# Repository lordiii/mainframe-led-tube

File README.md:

# TODO: README

See also:
https://github.com/XenGi/teensy_library

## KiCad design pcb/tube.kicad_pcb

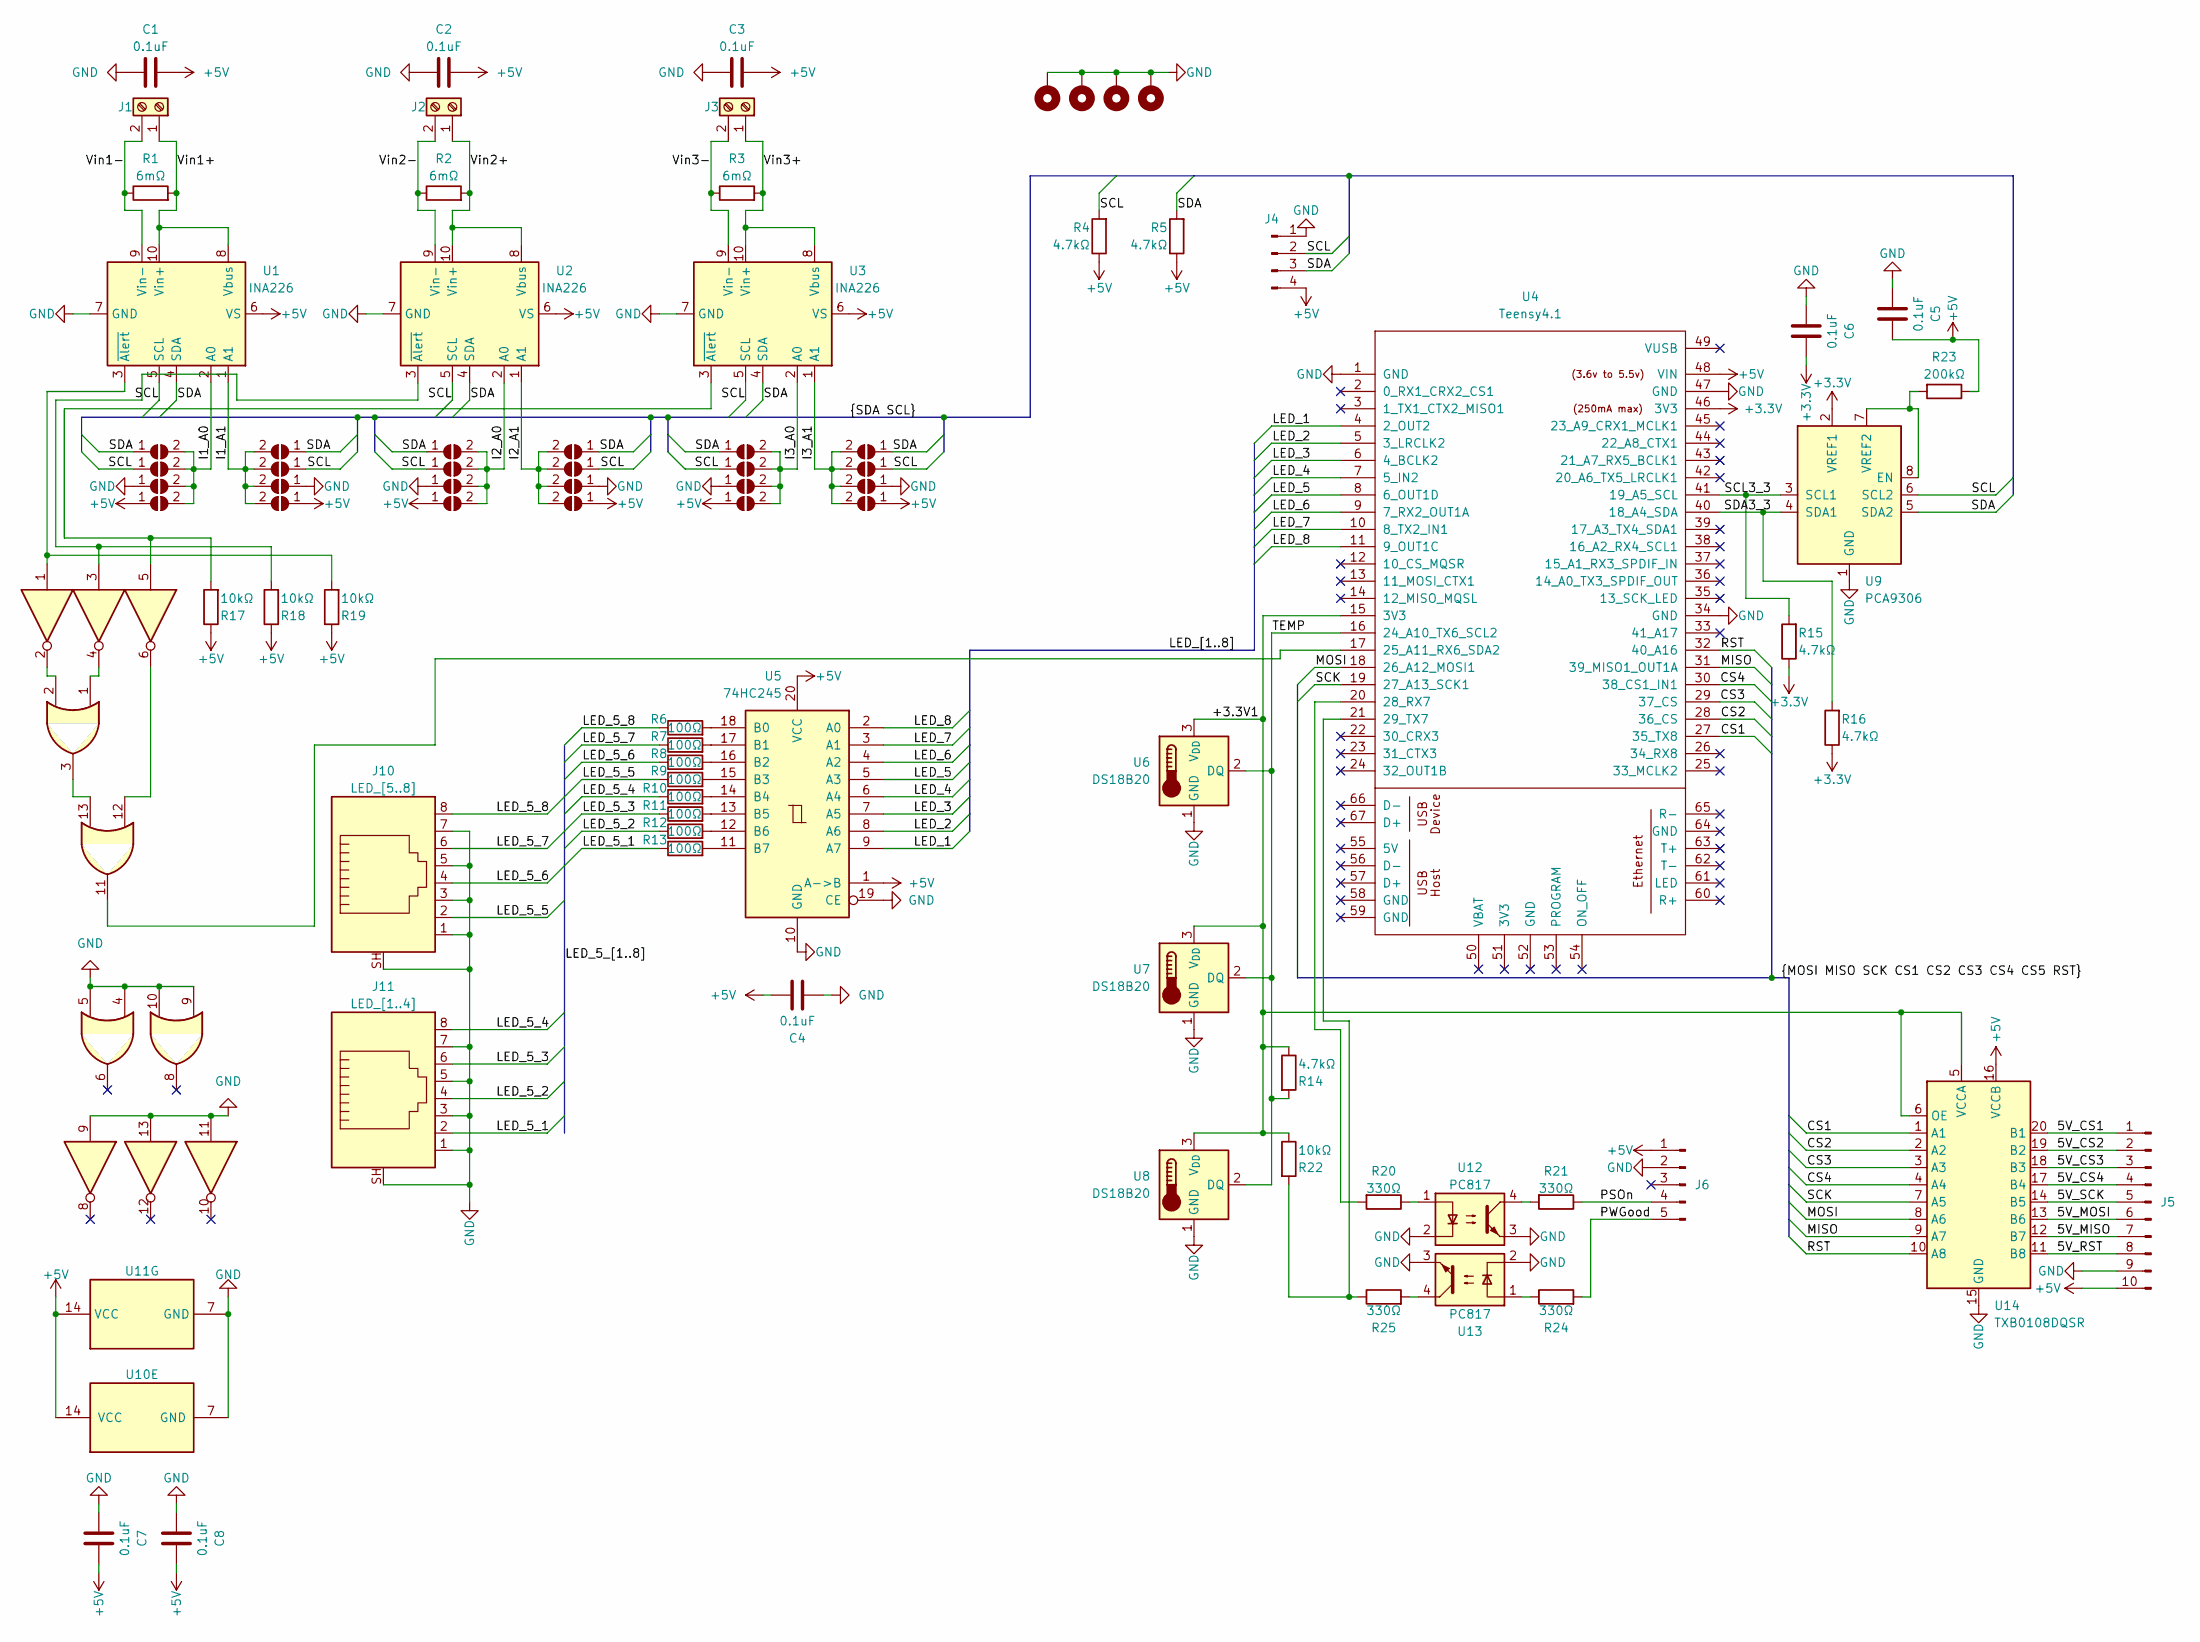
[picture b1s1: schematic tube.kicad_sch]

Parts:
C1, C2, C3, C4, C5, C6, C7, C8: 0.1uF; C_0805_2012Metric
H1, H2, H3, H4: MountingHole_Pad; MountingHole_2.2mm_M2_Pad
J1, J2, J3: Screw_Terminal_01x02; HB9500_1x02_P9.5mm_Screw_terminal
J4: Conn_01x04_Pin; PinHeader_1x04_P2.54mm_Vertical
J5: Conn_01x10_Pin; PinHeader_1x10_P2.54mm_Vertical
J6: Conn_01x05_Pin; 15EDG_Plug-in_Terminal_5x05_P2.54mm_Horizontal
J10: LED_[5..8]; RJ45_Ninigi_GE
J11: LED_[1..4]; RJ45_Ninigi_GE
JP1, JP2, JP3, JP4, JP5, JP6, JP7, JP8, JP9, JP10, JP11, JP12, JP13, JP14, JP15, JP16, JP17, JP18, JP19, JP20, JP21, JP22, JP23, JP24: SolderJumper_2_Open; SolderJumper-2_P1.3mm_Open_TrianglePad1.0x1.5mm
R1, R2, R3: 6mΩ; R_2512_6332Metric
R4, R5, R14, R15, R16: 4.7kΩ; R_0805_2012Metric
R6, R7, R8, R9, R10, R11, R12, R13: 100Ω; R_0805_2012Metric
R17, R18, R19, R22: 10kΩ; R_0805_2012Metric
R20, R21, R24, R25: 330Ω; R_0805_2012Metric
R23: 200kΩ; R_0805_2012Metric
U1, U2, U3: INA226; VSSOP-10_3x3mm_P0.5mm
U4: Teensy4.1; DIP-48_W15.24mm
U5: 74HC245; SSOP-20_4.4x6.5mm_P0.65mm
U6, U7, U8: DS18B20; PinHeader_1x03_P2.54mm_Vertical
U9: PCA9306; VSSOP-8_2.3x2mm_P0.5mm
U10: 74LS32; SO-14_3.9x8.65mm_P1.27mm
U11: 74AHC04; SO-14_3.9x8.65mm_P1.27mm
U12, U13: PC817; DIP-4_W7.62mm
U14: TXB0108DQSR; HTSSOP-20-1EP_4.4x6.5mm_P0.65mm_EP2.74x3.86mm

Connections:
+3.3V: C6.2, R15.1, R16.1, U4.46 (3V3), U9.2 (VREF1)
+5V: C1.2, C2.2, C3.2, C4.2, C5.2, C7.2, C8.2, J4.4, J5.10, J6.1, JP4.1 (A), JP8.1 (A), JP15.1 (A), JP16.1 (A), JP23.1 (A), JP24.1 (A), R4.1, R5.1, R17.1, R18.1, R19.1, R23.1, U1.6 (VS), U2.6 (VS), U3.6 (VS), U4.48 (VIN), U5.1 (A->B), U5.20 (VCC), U10.14 (VCC), U11.14 (VCC), U14.16 (VCCB)
/5V_CS1: J5.1, U14.20 (B1)
/5V_CS2: J5.2, U14.19 (B2)
/5V_CS3: J5.3, U14.18 (B3)
/5V_CS4: J5.4, U14.17 (B4)
/5V_MISO: J5.7, U14.12 (B7)
/5V_MOSI: J5.6, U14.13 (B6)
/5V_RST: J5.8, U14.11 (B8)
/5V_SCK: J5.5, U14.14 (B5)
/+3.3V1: R14.1, R22.1, U4.15 (3V3), U6.3 (V_{DD}), U7.3 (V_{DD}), U8.3 (V_{DD}), U14.5 (VCCA), U14.6 (OE)
/CS1: U4.27 (35_TX8), U14.1 (A1)
/CS2: U4.28 (36_CS), U14.2 (A2)
/CS3: U4.29 (37_CS), U14.3 (A3)
/CS4: U4.30 (38_CS1_IN1), U14.4 (A4)
/I1_A0: JP1.2 (B), JP2.2 (B), JP3.2 (B), JP4.2 (B), U1.2 (A0)
/I1_A1: JP5.2 (B), JP6.2 (B), JP7.2 (B), JP8.2 (B), U1.1 (A1)
/I2_A0: JP9.2 (B), JP11.2 (B), JP13.2 (B), JP15.2 (B), U2.2 (A0)
/I2_A1: JP10.2 (B), JP12.2 (B), JP14.2 (B), JP16.2 (B), U2.1 (A1)
/I3_A0: JP17.2 (B), JP19.2 (B), JP21.2 (B), JP23.2 (B), U3.2 (A0)
/I3_A1: JP18.2 (B), JP20.2 (B), JP22.2 (B), JP24.2 (B), U3.1 (A1)
/LED_1: U4.4 (2_OUT2), U5.9 (A7)
/LED_2: U4.5 (3_LRCLK2), U5.8 (A6)
/LED_3: U4.6 (4_BCLK2), U5.7 (A5)
/LED_4: U4.7 (5_IN2), U5.6 (A4)
/LED_5: U4.8 (6_OUT1D), U5.5 (A3)
/LED_5_1: J11.2, R13.1
/LED_5_2: J11.4, R12.1
/LED_5_3: J11.6, R11.1
/LED_5_4: J11.8, R10.1
/LED_5_5: J10.2, R9.1
/LED_5_6: J10.4, R8.1
/LED_5_7: J10.6, R7.1
/LED_5_8: J10.8, R6.1
/LED_6: U4.9 (7_RX2_OUT1A), U5.4 (A2)
/LED_7: U4.10 (8_TX2_IN1), U5.3 (A1)
/LED_8: U4.11 (9_OUT1C), U5.2 (A0)
/MISO: U4.31 (39_MISO1_OUT1A), U14.9 (A7)
/MOSI: U4.18 (26_A12_MOSI1), U14.8 (A6)
/PSOn: J6.4, R21.1
/PWGood: J6.5, R24.2
/RST: U4.32 (40_A16), U14.10 (A8)
/SCK: U4.19 (27_A13_SCK1), U14.7 (A5)
/SCL: J4.2, JP2.1 (A), JP6.1 (A), JP11.1 (A), JP12.1 (A), JP19.1 (A), JP20.1 (A), R4.2, U1.5 (SCL), U2.5 (SCL), U3.5 (SCL), U9.6 (SCL2)
/SCL3_3: R15.2, U4.41 (19_A5_SCL), U9.3 (SCL1)
/SDA: J4.3, JP1.1 (A), JP5.1 (A), JP9.1 (A), JP10.1 (A), JP17.1 (A), JP18.1 (A), R5.2, U1.4 (SDA), U2.4 (SDA), U3.4 (SDA), U9.5 (SDA2)
/SDA3_3: R16.2, U4.40 (18_A4_SDA), U9.4 (SDA1)
/TEMP: R14.2, U4.16 (24_A10_TX6_SCL2), U6.2 (DQ), U7.2 (DQ), U8.2 (DQ)
/Vin1+: J1.1, R1.2, U1.8 (Vbus), U1.10 (Vin+)
/Vin1-: J1.2, R1.1, U1.9 (Vin-)
/Vin2+: J2.1, R2.2, U2.8 (Vbus), U2.10 (Vin+)
/Vin2-: J2.2, R2.1, U2.9 (Vin-)
/Vin3+: J3.1, R3.2, U3.8 (Vbus), U3.10 (Vin+)
/Vin3-: J3.2, R3.1, U3.9 (Vin-)
GND: C1.1, C2.1, C3.1, C4.1, C5.1, C6.1, C7.1, C8.1, H1.1, H2.1, H3.1, H4.1, J4.1, J5.9, J6.2, J10.1, J10.3, J10.5, J10.7, J10.SH, J11.1, J11.3, J11.5, J11.7, J11.SH, JP3.1 (A), JP7.1 (A), JP13.1 (A), JP14.1 (A), JP21.1 (A), JP22.1 (A), U1.7 (GND), U2.7 (GND), U3.7 (GND), U4.1 (GND), U4.34 (GND), U4.47 (GND), U5.10 (GND), U5.19 (CE), U6.1 (GND), U7.1 (GND), U8.1 (GND), U9.1 (GND), U10.4, U10.5, U10.7 (GND), U10.9, U10.10, U11.7 (GND), U11.9, U11.11, U11.13, U12.2, U12.3, U13.2, U13.3, U14.15 (GND)
unnamed: R20.1, U12.1
unnamed: R21.2, U12.4
unnamed: R24.1, U13.1
unnamed: R25.2, U13.4
unnamed: R19.2, U1.3 (~Alert), U11.1
unnamed: R18.2, U2.3 (~Alert), U11.3
unnamed: R17.2, U3.3 (~Alert), U11.5
unnamed: U4.17 (25_A11_RX6_SDA2), U10.11
unnamed: R20.2, U4.20 (28_RX7)
unnamed: R22.2, R25.1, U4.21 (29_TX7)
unnamed: R6.2, U5.18 (B0)
unnamed: R7.2, U5.17 (B1)
unnamed: R8.2, U5.16 (B2)
unnamed: R9.2, U5.15 (B3)
unnamed: R10.2, U5.14 (B4)
unnamed: R11.2, U5.13 (B5)
unnamed: R12.2, U5.12 (B6)
unnamed: R13.2, U5.11 (B7)
unnamed: R23.2, U9.7 (VREF2), U9.8 (EN)
unnamed: U10.1, U11.4
unnamed: U10.2, U11.2
unnamed: U10.12, U11.6
unnamed: U10.3, U10.13

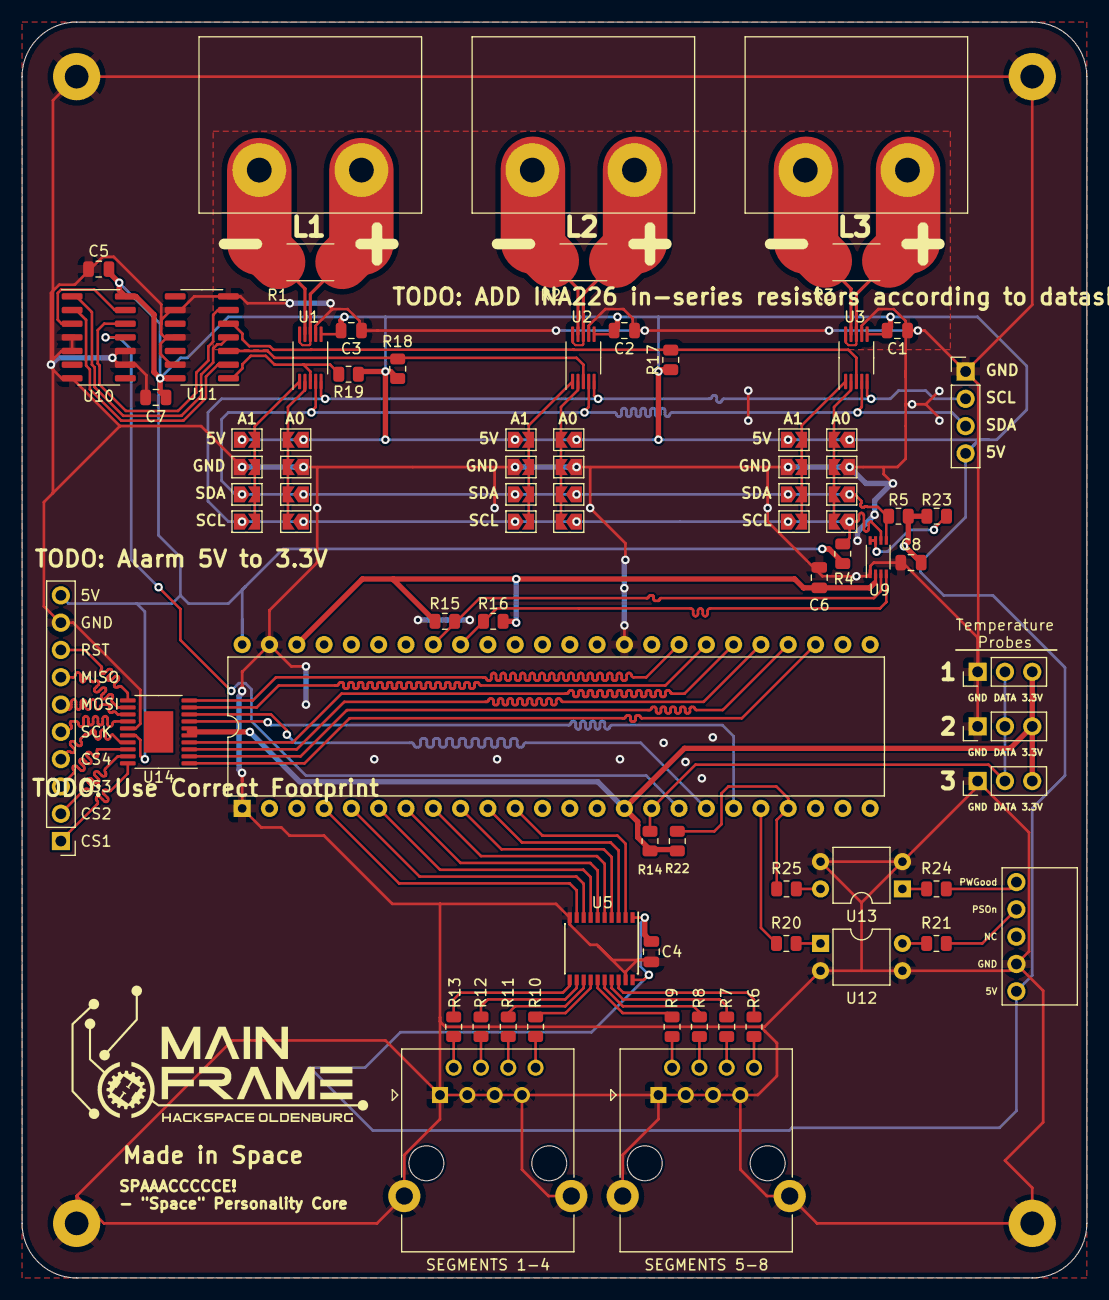
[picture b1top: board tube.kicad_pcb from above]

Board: 2 copper layers, 99.1 x 116.8 mm, 83 parts (0 on the bottom side), 78 nets.

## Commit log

2023-11-16 Init
2023-11-17 Refactor: Create PCB Subfolder
2023-11-17 Refactor: README.md
2023-11-17 Feature: Initialize PlatformIO
2023-11-17 Feature: Respond to ArtNet
2023-11-17 Feature: Add INA226 Library
2023-11-17 Refactor: Merge Files
2023-11-17 Feature: Poll DMX Data every 8000us
2023-11-17 Fix: NativeEthernet For ArtNet
2023-11-18 PCB: Reposition Power Supply
2023-11-18 Fix: Do not use IntervalTimer
2023-11-18 PCB: Bigger Shunt Traces
2023-11-18 PCB: Use 3.3V For Temperature Probes
2023-11-18 PCB: Add thermal reliefs
2023-11-18 PCB: Remove stray wire
2023-11-18 PCB: Use 0805
2023-11-18 PCB: Verify Pullups
2023-11-18 PCB: Tweak Shunt Traces
2023-11-18 PCB: Add Optocoppler For PWGood
2023-11-18 PCB: Tweak Shunt Trace
2023-11-18 PCB: Improve Power Traces
2023-11-18 PCB: Add 10k PWGood Pullup
2023-11-18 PCB: Length Matching
2023-11-18 PCB: Add SPI Voltage Shift
2023-11-19 PCB: Optimize Traces
2023-11-19 PCB: Update .gitignore
2023-11-19 PCB: Add SPI Silkscreen
2023-11-19 PCB: Remove Stray Silkscreen Text
2023-11-23 Firmware: Remove Artnet Support
2023-11-23 Firmware: Use QNEthernet
2023-11-26 Firmware: Read Temperatures
2023-11-26 Firmware: Prepare For SD Card
2023-11-28 Firmware: Cleanup .h
2023-11-29 Firmware: UART Terminal
2023-11-29 Firmware: Add Effect Modes
2023-11-29 Firmware: Rename Effects
2023-11-30 Firmware: Police Effect
2023-11-30 Firmware: Add Effect Files
2023-11-30 Firmware: Add Missing Defined To Globals
2023-11-30 Firmware: Simplify Frame Calculation
2023-11-30 Firmware: Add Basic Web Support
2023-11-30 Firmware: Dependency Hell
2023-11-30 Firmware: Brightness Control
2023-12-02 Firmware: Add Current Sense Command
2023-12-02 Firmware: Stream Web Files
2023-12-02 PCB: Fulfill PCA9306 Spec
2023-12-02 PCB: Add TODO notices
2023-12-03 Firmware: Fix Issues with current sensors
2023-12-03 PCB: Change Optocoupler Resistor Values
2023-12-03 Firmware: Power On Command
2023-12-04 Firmware: Define globals in header files
2023-12-04 Firmware: Easier Effect Registration
2023-12-04 Firmware: Fade Effects
2023-12-04 Firmware: Display Current Values
2023-12-04 Firmware: Resolve Merge Issues
2023-12-04 Firmware: Render Sensor Values on TFT
2023-12-04 Firmware: Beam Effect
2023-12-04 Firmware: Add Temperature Probe Adresses
2023-12-05 Firmware: Fix Sensor Ordering
2023-12-05 Firmware: Remove Usage of malloc
2023-12-05 Firmware: Define Effect Data
2023-12-06 Firmware: Utility Functions
2023-12-06 Firmware: Game of Life
2023-12-06 Firmware: Fix Game Of Life
2023-12-07 Firmware: Tetris Animation
2023-12-07 Firmware: Improve Tetris Collision Detection
2023-12-07 Firmware: Seperate Game Of Life Into Own Files
2023-12-07 Firmware: Prevent Duplicate Header File Inclusion
2023-12-07 Firmware: Movement Enum
2023-12-07 Firmware: Improve Tetris Collisions
2023-12-09 Firmware: Tetris
2023-12-10 Firmware: Controller Support
2023-12-11 Fire
2023-12-11 rotation
2023-12-11 pointer alignment
2023-12-11 pong beginning
2023-12-12 prevent pointers in union
2023-12-15 pong
2023-12-16 exchange cli tooling
2023-12-16 cleanup
2023-12-16 Helix Effect
2023-12-18 stream tube status to web
2023-12-18 set tube effect from web
2023-12-19 reenable sensor polling
2023-12-19 improve helix effects
2023-12-19 More Commands
2023-12-19 More Cleanup
2023-12-19 fix network info
2023-12-19 apply brightness to helix effects
2023-12-19 fixed all fade
2024-02-03 side beam
2024-02-03 default effect
2024-03-01 Firmware: Add Controller Arduino Sketch
2024-12-06 Project Cleanup
2024-12-06 prepare restructure
2024-12-11 Restructure + Code Cleanup
2024-12-14 Refactor sensor
2024-12-14 Refactor gamepads
2024-12-14 Use class for effect data
2024-12-15 Reenable tetris
2024-12-15 Reenable CLI
2024-12-15 Arrow pictogram effect
2024-12-15 Render TFT every 250ms
2024-12-17 Implement TFT Menus
2024-12-17 Clear controller on disconnect
2024-12-17 Allow controller menu navigation
2024-12-18 Refactor gamepad Communication
2024-12-18 Allow toggling power via display
2024-12-18 Remove old tft files
2024-12-18 Add .clang-format file
2024-12-18 Process analog gamepad values
2024-12-18 Show current effect
2024-12-18 Event based keybindings
2024-12-18 Perform render task in main loop
2024-12-18 Fix tetris button bindings
2024-12-18 Fix remaining tetris issues
2025-09-16 fix(led): optimize led functions
2025-09-16 fix(effects): remove tetris singleton
2025-09-16 fix(sensors): actually read temperature
2025-09-16 fix(effects): add missing dummy.cpp
2025-09-16 fix(cli): improve sensor logging
2025-09-26 feat(sensors): measure internal cpu temperature
2025-09-26 testing
2025-09-30 feat: prepare dynamic fx loading
2025-09-30 feat: add sd card support
2025-09-30 feat: add beam effect
2025-10-04 feat: init loading fx from sd
